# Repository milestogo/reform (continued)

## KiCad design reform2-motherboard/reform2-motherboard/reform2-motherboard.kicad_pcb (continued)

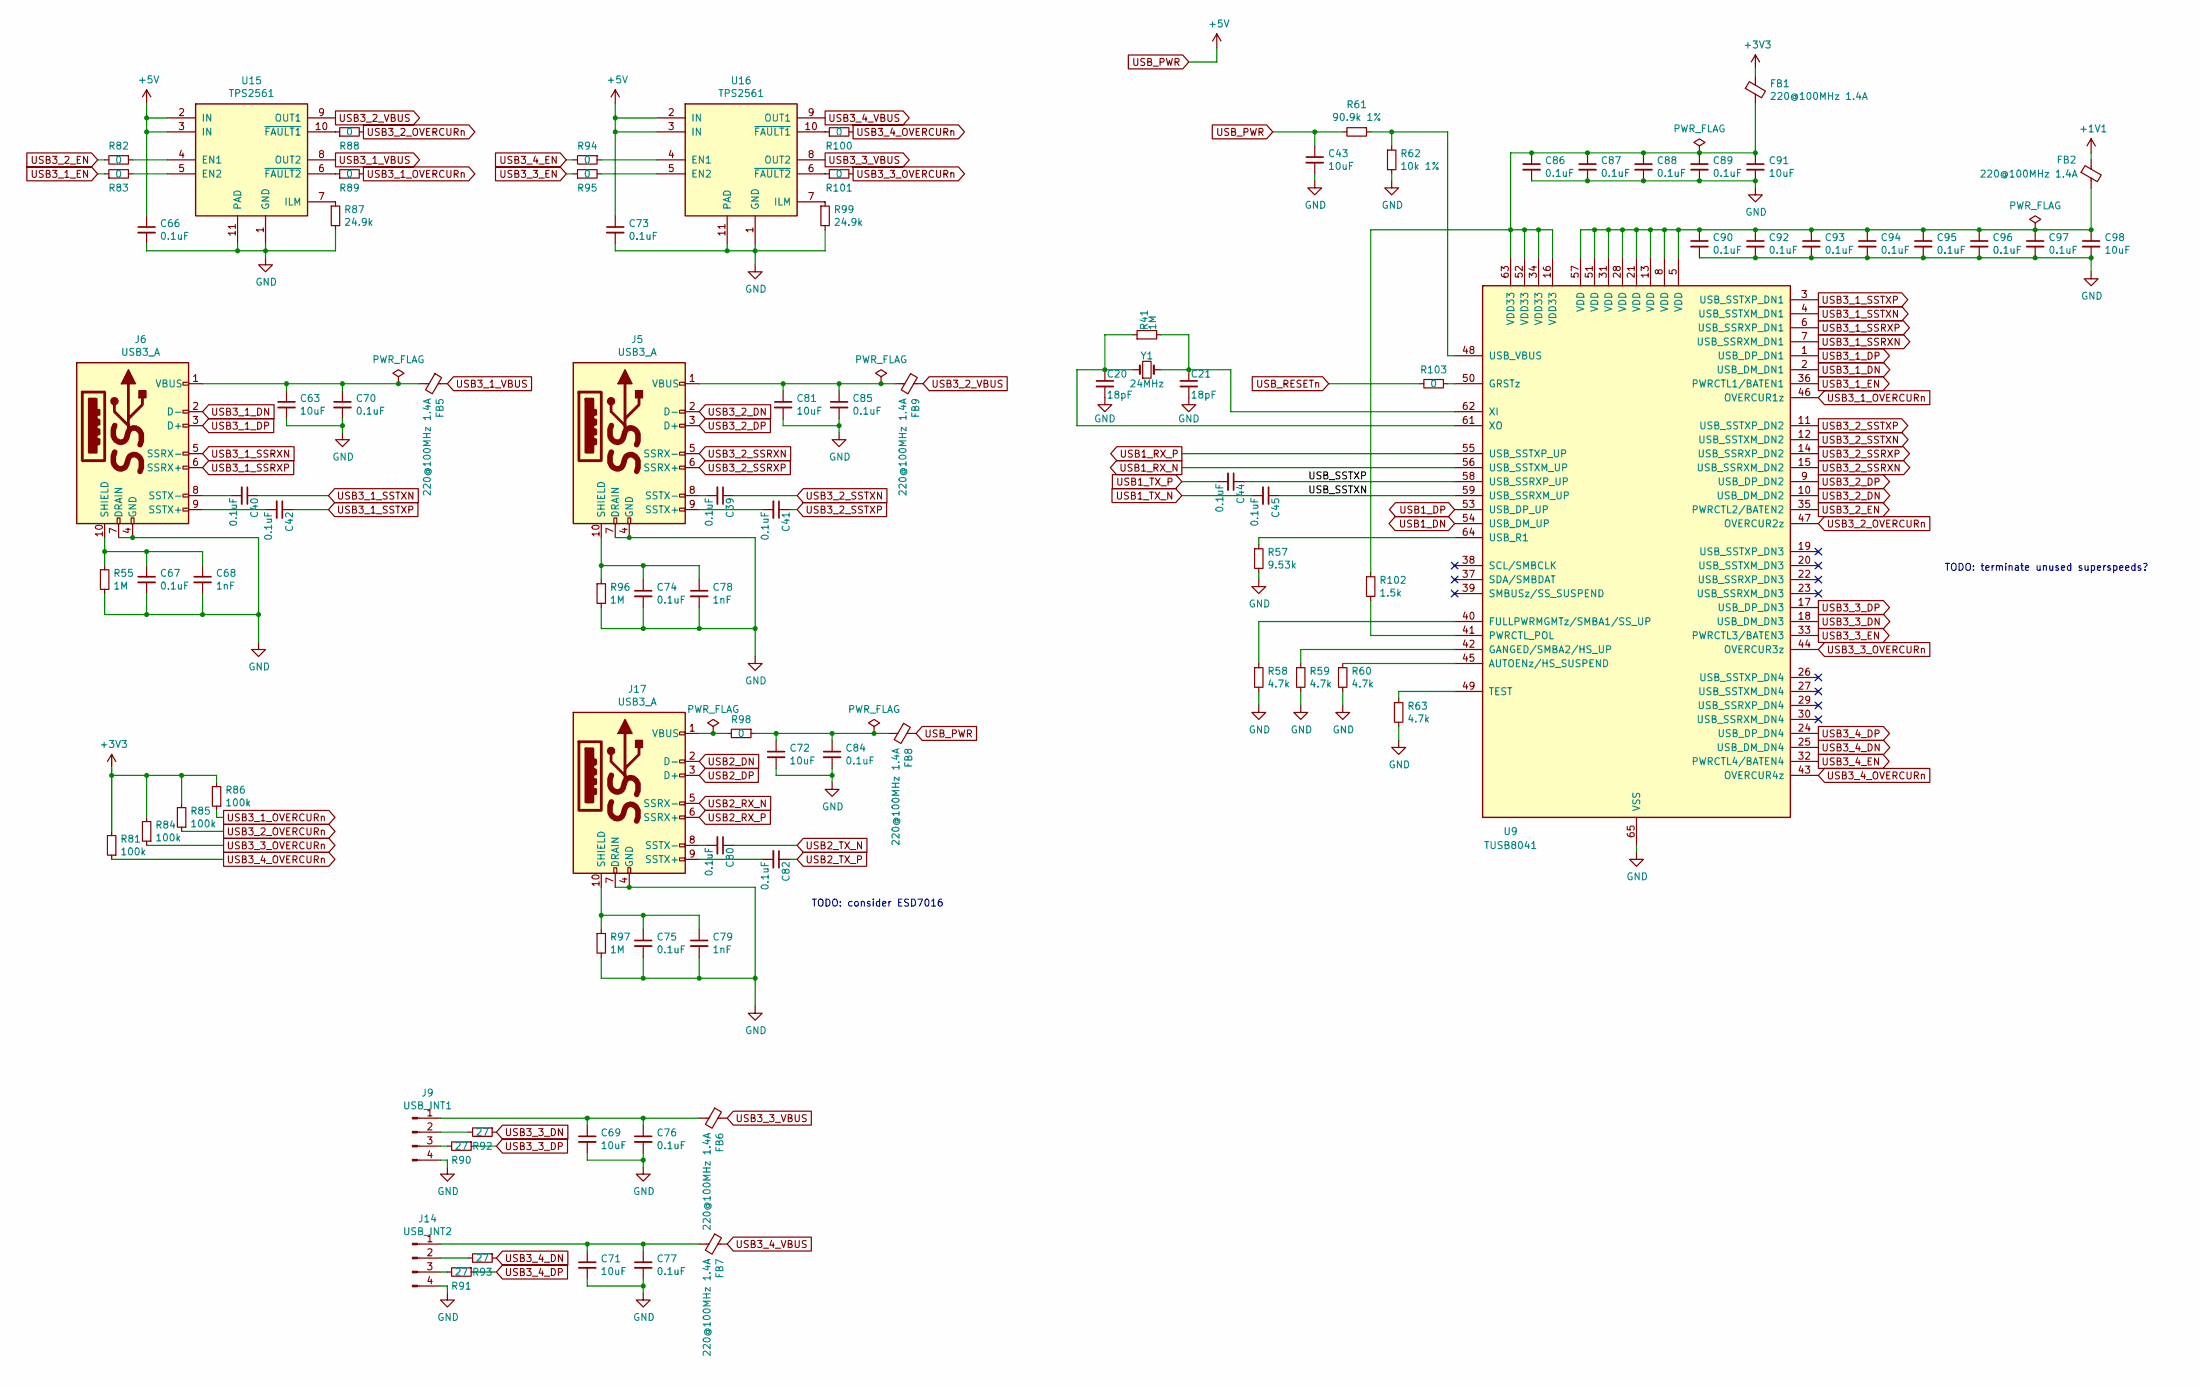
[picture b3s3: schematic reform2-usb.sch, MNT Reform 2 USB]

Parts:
C20, C21: 18pF; C_0603_1608Metric
C39, C40, C41, C42, C44, C45, C66, C67, C70, C73, C74, C75, C76, C77, C80, C82, C84, C85, C86, C87, C88, C89, C90, C92, C93, C94, C95, C96, C97: 0.1uF; C_0603_1608Metric
C43, C63, C69, C71, C72, C81, C91, C98: 10uF; C_0603_1608Metric
C68, C78, C79: 1nF; C_0603_1608Metric
FB1, FB2, FB5, FB6, FB7, FB8, FB9: 220@100MHz 1.4A; L_0603_1608Metric
J5, J6, J17: USB3_A; USB3_A_Molex_48393-001
J9: USB_INT1; PinHeader_1x04_P2.00mm_Horizontal
J14: USB_INT2; PinHeader_1x04_P2.00mm_Horizontal
R41, R55, R96, R97: 1M; R_0603_1608Metric
R57: 9.53k; R_0603_1608Metric
R58, R59, R60, R63: 4.7k; R_0603_1608Metric
R61: 90.9k 1%; R_0603_1608Metric
R62: 10k 1%; R_0603_1608Metric
R81, R84, R85, R86: 100k; R_0603_1608Metric
R82, R83, R88, R89, R94, R95, R98, R100, R101, R103: 0; R_0603_1608Metric
R87, R99: 24.9k; R_0603_1608Metric
R90, R91, R92, R93: 27; R_0603_1608Metric
R102: 1.5k; R_0603_1608Metric
U9: TUSB8041; QFN-64-1EP_9x9mm_P0.5mm_EP6x6mm_ThermalVias
U15, U16: TPS2561; VSON-10-1EP_3x3mm_P0.5mm_EP1.65x2.4mm_ThermalVias
Y1: 24MHz; Crystal_SMD_Abracon_ABM8G-4Pin_3.2x2.5mm

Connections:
+1V1: FB2.1; also elsewhere on the board
/Reform 2 USB/USB_SSTXN: C45.1, U9.59 (USB_SSRXM_UP)
/Reform 2 USB/USB_SSTXP: C44.1, U9.58 (USB_SSRXP_UP)
GND: C20.2, C21.2, C43.2, C63.2, C66.2, C67.2, C68.2, C69.2, C70.2, C71.2, C72.2, C73.2, C74.2, C75.2, C76.2, C77.2, C78.2, C79.2, C81.2, C84.2, C85.2, C86.2, C87.2, C88.2, C89.2, C90.2, C91.2, C92.2, C93.2, C94.2, C95.2, C96.2, C97.2, C98.2, J5.4 (GND), J5.7 (DRAIN), J6.4 (GND), J6.7 (DRAIN), J9.4, J14.4, J17.4 (GND), J17.7 (DRAIN), R55.2, R57.2, R58.2, R59.2, R60.2, R62.2, R63.2, R87.2, R96.2, R97.2, R99.2, U9.65 (VSS), U15.1 (GND), U15.11 (PAD), U16.1 (GND), U16.11 (PAD); also elsewhere on the board
unnamed: C20.1, R41.1, U9.61 (XO), Y1.1
unnamed: C21.1, R41.2, U9.62 (XI), Y1.2
unnamed: C39.2, J5.8 (SSTX-)
unnamed: C40.2, J6.8 (SSTX-)
unnamed: C41.2, J5.9 (SSTX+)
unnamed: C42.2, J6.9 (SSTX+)
unnamed: C63.1, C70.1, FB5.2, J6.1 (VBUS)
unnamed: C67.1, C68.1, J6.10 (SHIELD), R55.1
unnamed: C69.1, C76.1, FB6.2, J9.1
unnamed: C71.1, C77.1, FB7.2, J14.1
unnamed: C72.1, C84.1, FB8.2, R98.1
unnamed: C74.1, C78.1, J5.10 (SHIELD), R96.1
unnamed: C75.1, C79.1, J17.10 (SHIELD), R97.1
unnamed: C80.2, J17.8 (SSTX-)
unnamed: C81.1, C85.1, FB9.2, J5.1 (VBUS)
unnamed: C82.2, J17.9 (SSTX+)
unnamed: C86.1, C87.1, C88.1, C89.1, C91.1, FB1.2, R102.1, U9.16 (VDD33), U9.34 (VDD33), U9.52 (VDD33), U9.63 (VDD33)
unnamed: C90.1, C92.1, C93.1, C94.1, C95.1, C96.1, C97.1, C98.1, FB2.2, U9.5 (VDD), U9.8 (VDD), U9.13 (VDD), U9.21 (VDD), U9.28 (VDD), U9.31 (VDD), U9.51 (VDD), U9.57 (VDD)
unnamed: J9.2, R92.2
unnamed: J9.3, R90.2
unnamed: J14.2, R93.2
unnamed: J14.3, R91.2
unnamed: J17.1 (VBUS), R98.2
unnamed: R57.1, U9.64 (USB_R1)
unnamed: R58.1, U9.40 (FULLPWRMGMTz/SMBA1/SS_UP)
unnamed: R59.1, U9.42 (GANGED/SMBA2/HS_UP)
unnamed: R60.1, U9.45 (AUTOENz/HS_SUSPEND)
unnamed: R61.1, R62.1, U9.48 (USB_VBUS)
unnamed: R63.1, U9.49 (TEST)
unnamed: R82.1, U15.4 (EN1)
unnamed: R83.2, U15.5 (EN2)
unnamed: R87.1, U15.7 (ILM)
unnamed: R88.1, U15.10 (~FAULT1)
unnamed: R89.1, U15.6 (~FAULT2)
unnamed: R94.1, U16.4 (EN1)
unnamed: R95.2, U16.5 (EN2)
unnamed: R99.1, U16.7 (ILM)
unnamed: R100.1, U16.10 (~FAULT1)
unnamed: R101.1, U16.6 (~FAULT2)
unnamed: R102.2, U9.41 (PWRCTL_POL)
unnamed: R103.1, U9.50 (GRSTz)
USB1_DN: U9.54 (USB_DM_UP); also elsewhere on the board
USB1_DP: U9.53 (USB_DP_UP); also elsewhere on the board
USB1_RX_N: U9.56 (USB_SSTXM_UP); also elsewhere on the board
USB1_RX_P: U9.55 (USB_SSTXP_UP); also elsewhere on the board
USB1_TX_N: C45.2; also elsewhere on the board
USB1_TX_P: C44.2; also elsewhere on the board
USB2_DN: J17.2 (D-); also elsewhere on the board
USB2_DP: J17.3 (D+); also elsewhere on the board
USB2_RX_N: J17.5 (SSRX-); also elsewhere on the board
USB2_RX_P: J17.6 (SSRX+); also elsewhere on the board
USB2_TX_N: C80.1; also elsewhere on the board
USB2_TX_P: C82.1; also elsewhere on the board
USB3_1_DN: J6.2 (D-), U9.2 (USB_DM_DN1)
USB3_1_DP: J6.3 (D+), U9.1 (USB_DP_DN1)
USB3_1_EN: R83.1, U9.36 (PWRCTL1/BATEN1)
USB3_1_OVERCURn: R86.1, R89.2, U9.46 (OVERCUR1z)
USB3_1_SSRXN: J6.5 (SSRX-), U9.7 (USB_SSRXM_DN1)
USB3_1_SSRXP: J6.6 (SSRX+), U9.6 (USB_SSRXP_DN1)
USB3_1_SSTXN: C40.1, U9.4 (USB_SSTXM_DN1)
USB3_1_SSTXP: C42.1, U9.3 (USB_SSTXP_DN1)
USB3_1_VBUS: FB5.1, U15.8 (OUT2)
USB3_2_DN: J5.2 (D-), U9.10 (USB_DM_DN2)
USB3_2_DP: J5.3 (D+), U9.9 (USB_DP_DN2)
USB3_2_EN: R82.2, U9.35 (PWRCTL2/BATEN2)
USB3_2_OVERCURn: R85.1, R88.2, U9.47 (OVERCUR2z)
USB3_2_SSRXN: J5.5 (SSRX-), U9.15 (USB_SSRXM_DN2)
USB3_2_SSRXP: J5.6 (SSRX+), U9.14 (USB_SSRXP_DN2)
USB3_2_SSTXN: C39.1, U9.12 (USB_SSTXM_DN2)
USB3_2_SSTXP: C41.1, U9.11 (USB_SSTXP_DN2)
USB3_2_VBUS: FB9.1, U15.9 (OUT1)
USB3_3_DN: R92.1, U9.18 (USB_DM_DN3)
USB3_3_DP: R90.1, U9.17 (USB_DP_DN3)
USB3_3_EN: R95.1, U9.33 (PWRCTL3/BATEN3)
USB3_3_OVERCURn: R84.1, R101.2, U9.44 (OVERCUR3z)
USB3_3_VBUS: FB6.1, U16.8 (OUT2)
USB3_4_DN: R93.1, U9.25 (USB_DM_DN4)
USB3_4_DP: R91.1, U9.24 (USB_DP_DN4)
USB3_4_EN: R94.2, U9.32 (PWRCTL4/BATEN4)
USB3_4_OVERCURn: R81.1, R100.2, U9.43 (OVERCUR4z)
USB3_4_VBUS: FB7.1, U16.9 (OUT1)
USB_PWR: C43.1, C66.1, C73.1, FB8.1, R61.2, U15.2 (IN), U15.3 (IN), U16.2 (IN), U16.3 (IN); also elsewhere on the board
USB_RESETn: R103.2; also elsewhere on the board

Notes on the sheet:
TODO: consider ESD7016
TODO: terminate unused superspeeds?

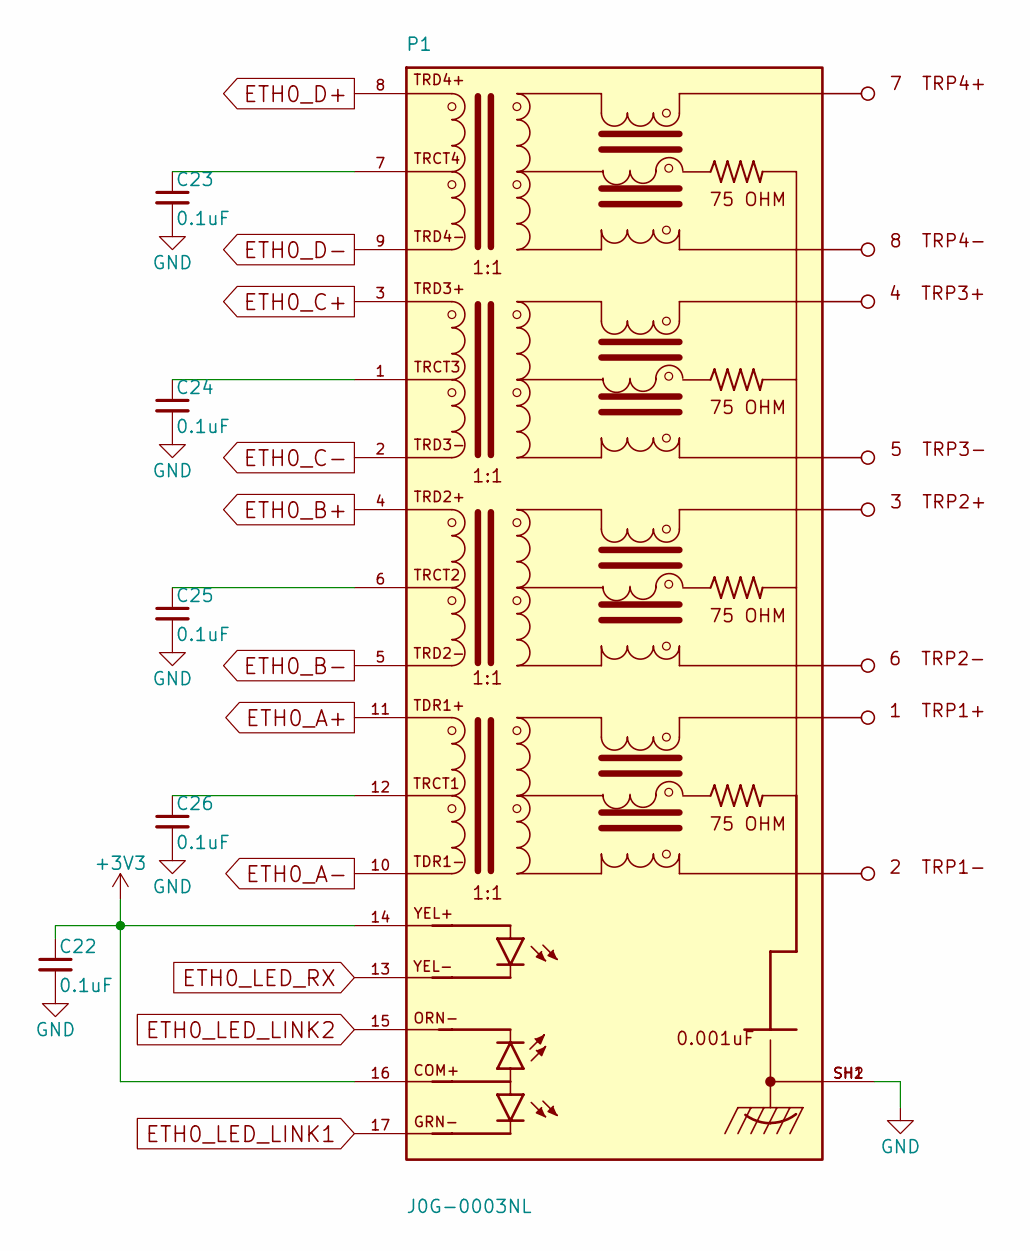
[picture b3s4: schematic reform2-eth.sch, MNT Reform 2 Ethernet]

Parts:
C22, C23, C24, C25, C26: 0.1uF; C_0603_1608Metric
P1: J0G-0003NL; PULSE_J0G-0003NL

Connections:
ETH0_A+: P1.11 (TDR1+); also elsewhere on the board
ETH0_A-: P1.10 (TDR1-); also elsewhere on the board
ETH0_B+: P1.4 (TRD2+); also elsewhere on the board
ETH0_B-: P1.5 (TRD2-); also elsewhere on the board
ETH0_C+: P1.3 (TRD3+); also elsewhere on the board
ETH0_C-: P1.2 (TRD3-); also elsewhere on the board
ETH0_D+: P1.8 (TRD4+); also elsewhere on the board
ETH0_D-: P1.9 (TRD4-); also elsewhere on the board
ETH0_LED_LINK1: P1.17 (GRN-); also elsewhere on the board
ETH0_LED_LINK2: P1.15 (ORN-); also elsewhere on the board
ETH0_LED_RX: P1.13 (YEL-); also elsewhere on the board
GND: C22.2, C23.2, C24.2, C25.2, C26.2, P1.SH1 (SHIELD), P1.SH2 (SHIELD); also elsewhere on the board
unnamed: C23.1, P1.7 (TRCT4)
unnamed: C24.1, P1.1 (TRCT3)
unnamed: C25.1, P1.6 (TRCT2)
unnamed: C26.1, P1.12 (TRCT1)

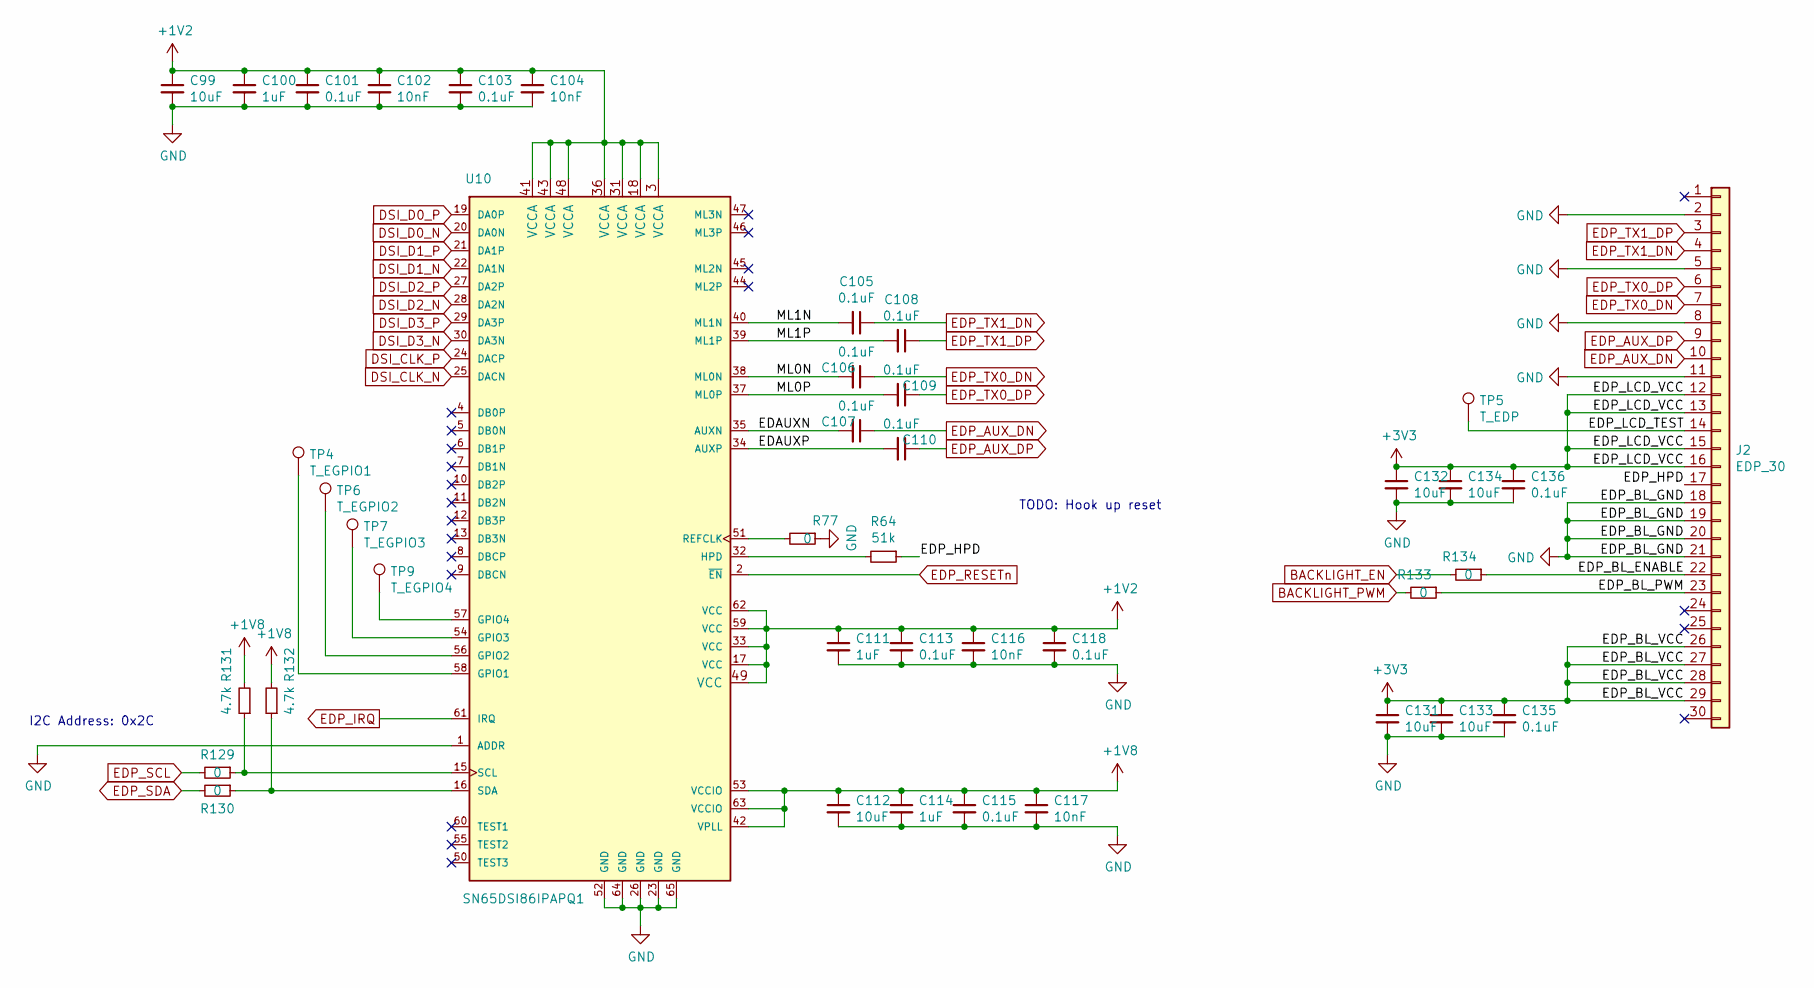
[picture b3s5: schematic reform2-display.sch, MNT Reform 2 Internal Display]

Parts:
C99, C112, C131, C132, C133, C134: 10uF; C_0603_1608Metric
C100, C111, C114: 1uF; C_0603_1608Metric
C101, C103, C105, C106, C107, C108, C109, C110, C113, C115, C118, C135, C136: 0.1uF; C_0603_1608Metric
C102, C104, C116, C117: 10nF; C_0603_1608Metric
J2: EDP_30; Hirose_FH12-30S-0.5SH_1x30-1MP_P0.50mm_Horizontal
R64: 51k; R_0603_1608Metric
R77, R129, R130, R133, R134: 0; R_0603_1608Metric
R131, R132: 4.7k; R_0603_1608Metric
TP4: T_EGPIO1; TestPoint_Pad_D1.0mm
TP5: T_EDP; TestPoint_Pad_D1.0mm
TP6: T_EGPIO2; TestPoint_Pad_D1.0mm
TP7: T_EGPIO3; TestPoint_Pad_D1.0mm
TP9: T_EGPIO4; TestPoint_Pad_D1.0mm
U10: SN65DSI86IPAPQ1; HTQFP-64-1EP_10x10mm_P0.5mm_EP8x8mm

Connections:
+1V2: C99.1, C100.1, C101.1, C102.1, C103.1, C104.1, C111.1, C113.1, C116.1, C118.1, U10.3 (VCCA), U10.17 (VCC), U10.18 (VCCA), U10.31 (VCCA), U10.33 (VCC), U10.36 (VCCA), U10.41 (VCCA), U10.43 (VCCA), U10.48 (VCCA), U10.49 (VCC), U10.59 (VCC), U10.62 (VCC); also elsewhere on the board
+1V8: C112.1, C114.1, C115.1, C117.1, R131.2, R132.2, U10.42 (VPLL), U10.53 (VCCIO), U10.63 (VCCIO); also elsewhere on the board
/Reform 2 Display/EDAUXN: C107.2, U10.35 (AUXN)
/Reform 2 Display/EDAUXP: C110.2, U10.34 (AUXP)
/Reform 2 Display/EDP_BL_ENABLE: J2.22, R134.1
/Reform 2 Display/EDP_BL_PWM: J2.23, R133.1
/Reform 2 Display/EDP_HPD: J2.17, R64.1
/Reform 2 Display/EDP_LCD_TEST: J2.14, TP5.1
/Reform 2 Display/ML0N: C106.2, U10.38 (ML0N)
/Reform 2 Display/ML0P: C109.2, U10.37 (ML0P)
/Reform 2 Display/ML1N: C105.2, U10.40 (ML1N)
/Reform 2 Display/ML1P: C108.2, U10.39 (ML1P)
BACKLIGHT_EN: R134.2; also elsewhere on the board
BACKLIGHT_PWM: R133.2; also elsewhere on the board
DSI_CLK_N: U10.25 (DACN); also elsewhere on the board
DSI_CLK_P: U10.24 (DACP); also elsewhere on the board
DSI_D0_N: U10.20 (DA0N); also elsewhere on the board
DSI_D0_P: U10.19 (DA0P); also elsewhere on the board
DSI_D1_N: U10.22 (DA1N); also elsewhere on the board
DSI_D1_P: U10.21 (DA1P); also elsewhere on the board
DSI_D2_N: U10.28 (DA2N); also elsewhere on the board
DSI_D2_P: U10.27 (DA2P); also elsewhere on the board
DSI_D3_N: U10.30 (DA3N); also elsewhere on the board
DSI_D3_P: U10.29 (DA3P); also elsewhere on the board
EDP_AUX_DN: C107.1, J2.10
EDP_AUX_DP: C110.1, J2.9
EDP_IRQ: U10.61 (IRQ); also elsewhere on the board
EDP_RESETn: U10.2 (~EN~); also elsewhere on the board
EDP_SCL: R129.2; also elsewhere on the board
EDP_SDA: R130.2; also elsewhere on the board
EDP_TX0_DN: C106.1, J2.7
EDP_TX0_DP: C109.1, J2.6
EDP_TX1_DN: C105.1, J2.4
EDP_TX1_DP: C108.1, J2.3
GND: C99.2, C100.2, C101.2, C102.2, C103.2, C104.2, C111.2, C112.2, C113.2, C114.2, C115.2, C116.2, C117.2, C118.2, C131.2, C132.2, C133.2, C134.2, C135.2, C136.2, J2.2, J2.5, J2.8, J2.11, J2.18, J2.19, J2.20, J2.21, R77.1, U10.1 (ADDR), U10.23 (GND), U10.26 (GND), U10.52 (GND), U10.64 (GND), U10.65 (GND); also elsewhere on the board
unnamed: R64.2, U10.32 (HPD)
unnamed: R77.2, U10.51 (REFCLK)
unnamed: R129.1, R131.1, U10.15 (SCL)
unnamed: R130.1, R132.1, U10.16 (SDA)
unnamed: TP4.1, U10.58 (GPIO1)
unnamed: TP6.1, U10.56 (GPIO2)
unnamed: TP7.1, U10.54 (GPIO3)
unnamed: TP9.1, U10.57 (GPIO4)

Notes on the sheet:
TODO: Hook up reset
I2C Address: 0x2C

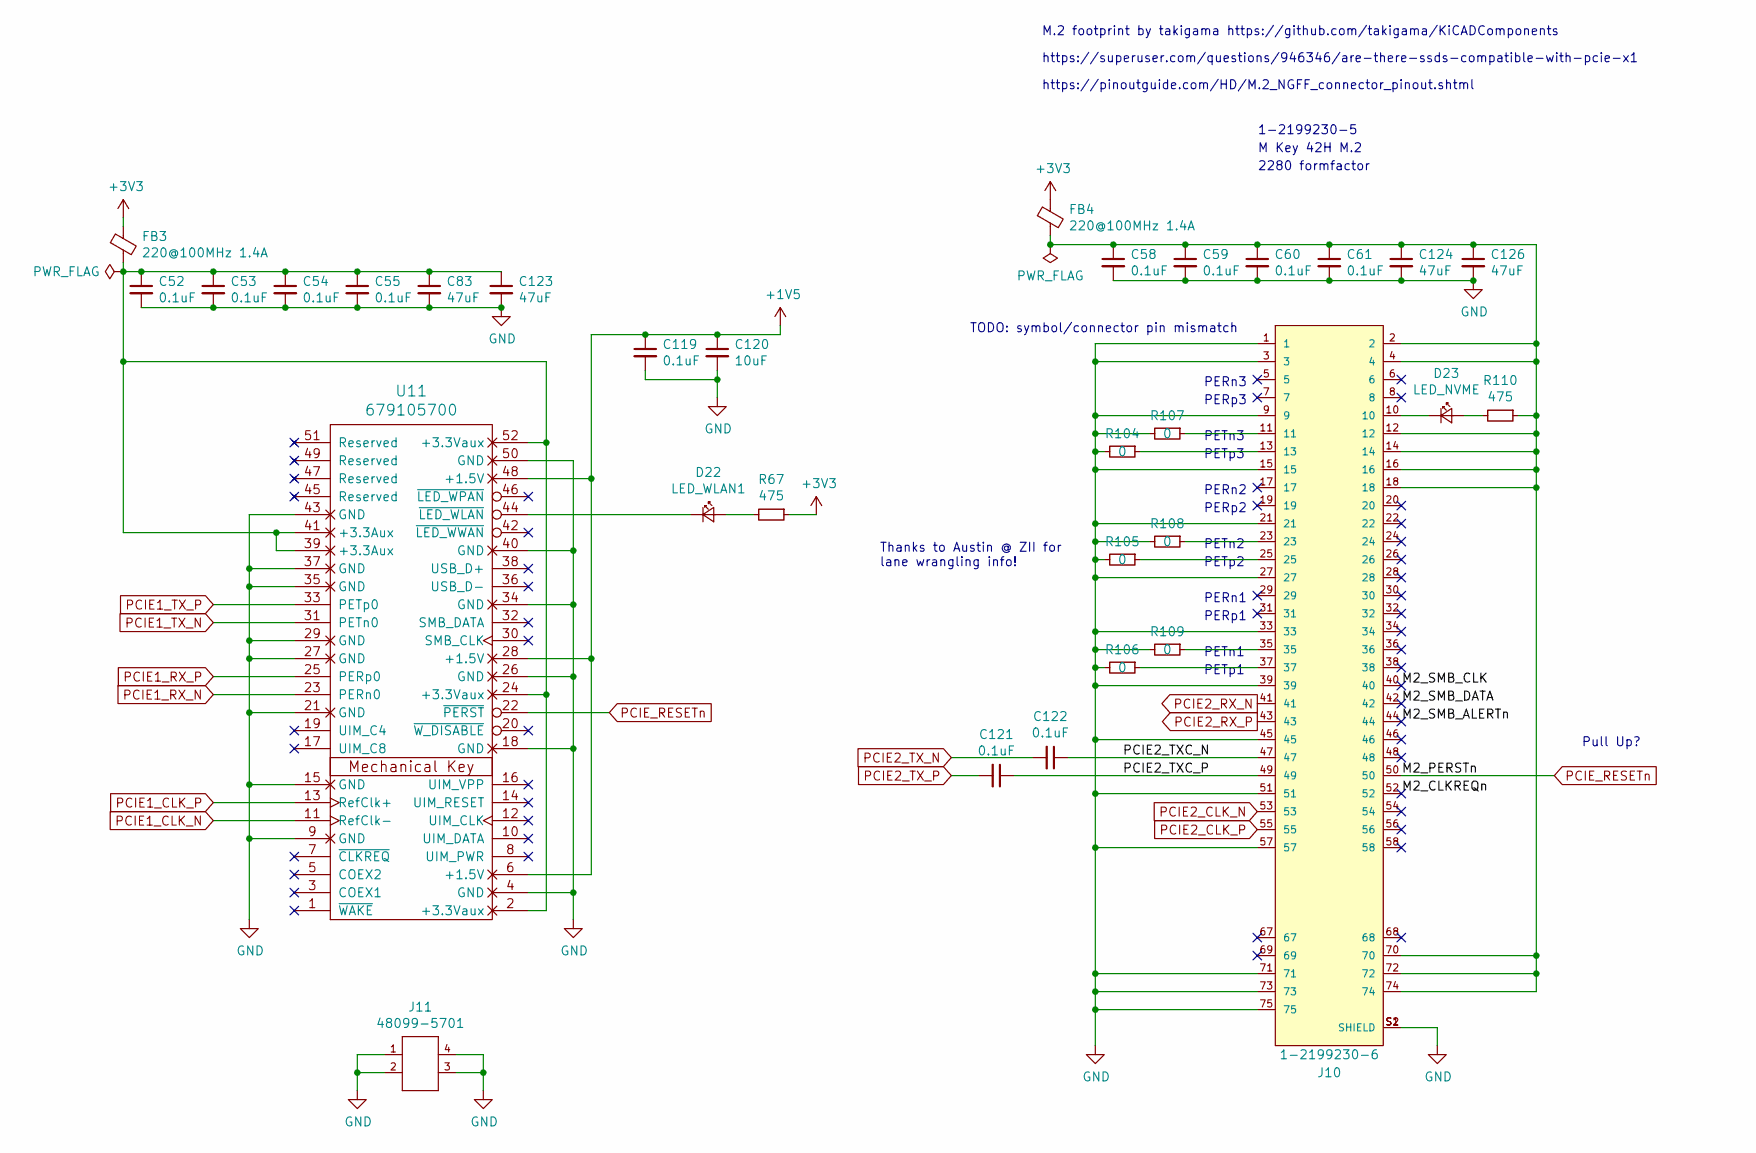
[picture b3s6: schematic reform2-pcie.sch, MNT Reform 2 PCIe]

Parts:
C52, C53, C54, C55, C58, C59, C60, C61, C119, C121, C122: 0.1uF; C_0603_1608Metric
C83, C123, C124, C126: 47uF; C_0603_1608Metric
C120: 10uF; C_0603_1608Metric
D22: LED_WLAN1; LED_0603_1608Metric
D23: LED_NVME; LED_0603_1608Metric
FB3, FB4: 220@100MHz 1.4A; L_0603_1608Metric
J10: 1-2199230-6; TE_1-2199230-6
J11: 48099-5701; MOLEX_48099-5701
R67, R110: 475; R_0603_1608Metric
R104, R105, R106, R107, R108, R109: 0; R_0603_1608Metric
U11: 679105700; MOLEX_67910-5700

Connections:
+1V5: C119.1, C120.1, U11.6 (+1.5V), U11.28 (+1.5V), U11.48 (+1.5V); also elsewhere on the board
/Reform 2 PCIe/M2_CLKREQn: J10.52
/Reform 2 PCIe/M2_SMB_ALERTn: J10.44
/Reform 2 PCIe/M2_SMB_CLK: J10.40
/Reform 2 PCIe/M2_SMB_DATA: J10.42
/Reform 2 PCIe/PCIE2_TXC_N: C122.1, J10.47
/Reform 2 PCIe/PCIE2_TXC_P: C121.1, J10.49
GND: C52.2, C53.2, C54.2, C55.2, C58.2, C59.2, C60.2, C61.2, C83.2, C119.2, C120.2, C123.2, C124.2, C126.2, J10.1, J10.3, J10.9, J10.15, J10.21, J10.27, J10.33, J10.39, J10.45, J10.51, J10.57, J10.71, J10.73, J10.75, J10.S1 (SHIELD), J10.S2 (SHIELD), J11.1, J11.2, J11.3, J11.4, R104.2, R105.2, R106.2, R107.2, R108.2, R109.2, U11.4 (GND), U11.9 (GND), U11.15 (GND), U11.18 (GND), U11.21 (GND), U11.26 (GND), U11.27 (GND), U11.29 (GND), U11.34 (GND), U11.35 (GND), U11.37 (GND), U11.40 (GND), U11.43 (GND), U11.50 (GND); also elsewhere on the board
unnamed: C52.1, C53.1, C54.1, C55.1, C83.1, C123.1, FB3.2, U11.2 (+3.3Vaux), U11.24 (+3.3Vaux), U11.39 (+3.3Aux), U11.41 (+3.3Aux), U11.52 (+3.3Vaux)
unnamed: C58.1, C59.1, C60.1, C61.1, C124.1, C126.1, FB4.2, J10.2, J10.4, J10.12, J10.14, J10.16, J10.18, J10.70, J10.72, J10.74, R110.1
unnamed: D22.1 (K), U11.44 (~LED_WLAN)
unnamed: D22.2 (A), R67.2
unnamed: D23.1 (K), J10.10
unnamed: D23.2 (A), R110.2
unnamed: J10.11, R107.1
unnamed: J10.13, R104.1
unnamed: J10.23, R108.1
unnamed: J10.25, R105.1
unnamed: J10.35, R109.1
unnamed: J10.37, R106.1
PCIE1_CLK_N: U11.11 (RefClk-); also elsewhere on the board
PCIE1_CLK_P: U11.13 (RefClk+); also elsewhere on the board
PCIE1_RX_N: U11.23 (PERn0); also elsewhere on the board
PCIE1_RX_P: U11.25 (PERp0); also elsewhere on the board
PCIE1_TX_N: U11.31 (PETn0); also elsewhere on the board
PCIE1_TX_P: U11.33 (PETp0); also elsewhere on the board
PCIE2_CLK_N: J10.53; also elsewhere on the board
PCIE2_CLK_P: J10.55; also elsewhere on the board
PCIE2_RX_N: J10.41; also elsewhere on the board
PCIE2_RX_P: J10.43; also elsewhere on the board
PCIE2_TX_N: C122.2; also elsewhere on the board
PCIE2_TX_P: C121.2; also elsewhere on the board
PCIE_RESETn: J10.50, U11.22 (~PERST); also elsewhere on the board

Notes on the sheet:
1-2199230-5
M Key 42H M.2
2280 formfactor
M.2 footprint by takigama https://github.com/takigama/KiCADComponents
https://superuser.com/questions/946346/are-there-ssds-compatible-with-pcie-x1
https://pinoutguide.com/HD/M.2_NGFF_connector_pinout.shtml
Pull Up?
PERn1
PERp1
PETp2
PETn2
PETn1
PETp1
PERn2
PERp2
PETp3
PETn3
PERn3
PERp3
Thanks to Austin @ ZII for lane wrangling info!
TODO: symbol/connector pin mismatch

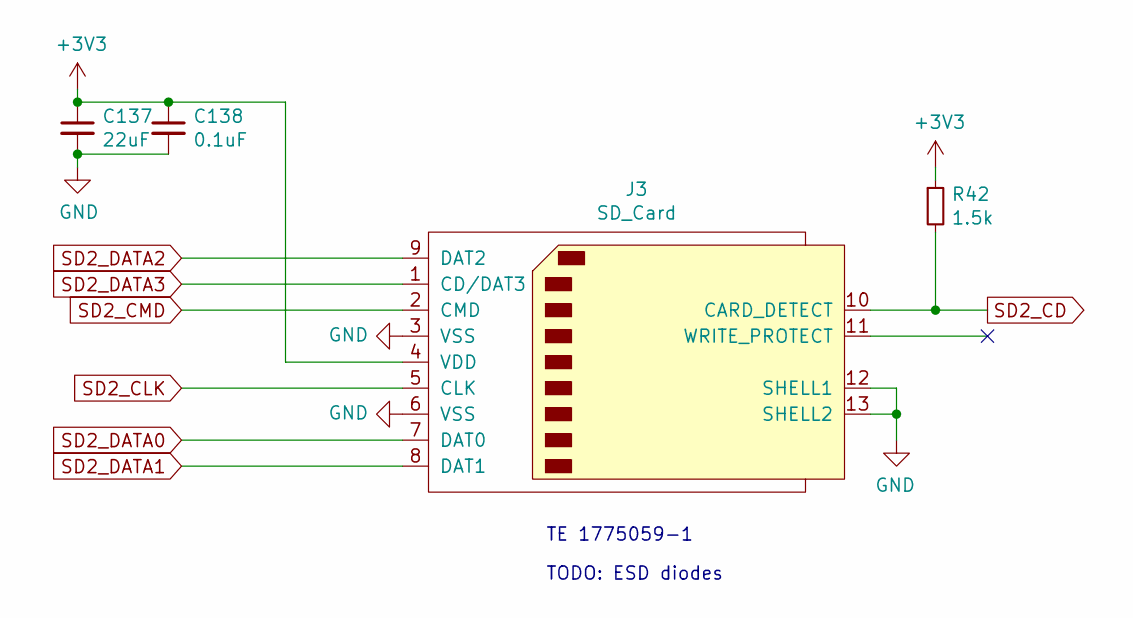
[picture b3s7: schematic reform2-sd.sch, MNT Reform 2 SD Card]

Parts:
C137: 22uF; C_0603_1608Metric
C138: 0.1uF; C_0603_1608Metric
J3: SD_Card; TE_1775059-1
R42: 1.5k; R_0603_1608Metric

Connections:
GND: C137.2, C138.2, J3.3 (VSS), J3.6 (VSS), J3.12 (SHELL1), J3.13 (SHELL2); also elsewhere on the board
SD2_CD: J3.10 (CARD_DETECT), R42.2; also elsewhere on the board
SD2_CLK: J3.5 (CLK); also elsewhere on the board
SD2_CMD: J3.2 (CMD); also elsewhere on the board
SD2_DATA0: J3.7 (DAT0); also elsewhere on the board
SD2_DATA1: J3.8 (DAT1); also elsewhere on the board
SD2_DATA2: J3.9 (DAT2); also elsewhere on the board
SD2_DATA3: J3.1 (CD/DAT3); also elsewhere on the board

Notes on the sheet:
TODO: ESD diodes
TE 1775059-1

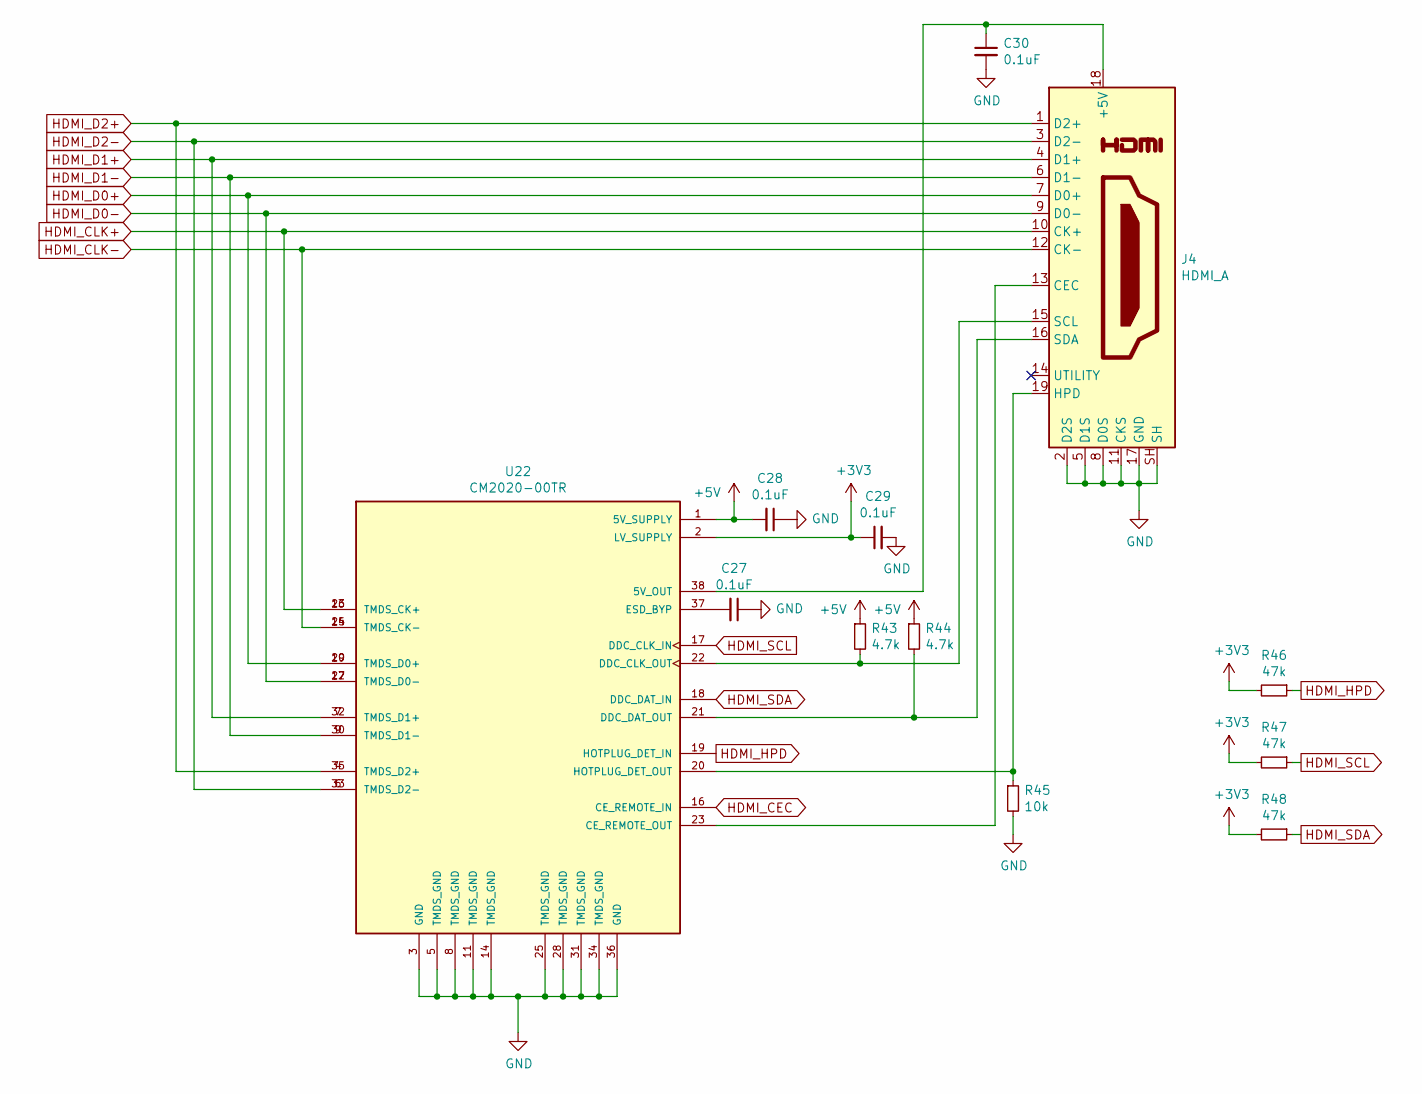
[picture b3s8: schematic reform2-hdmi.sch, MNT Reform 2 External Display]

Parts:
C27, C28, C29, C30: 0.1uF; C_0603_1608Metric
J4: HDMI_A; HDMI-685119134923
R43, R44: 4.7k; R_0603_1608Metric
R45: 10k; R_0603_1608Metric
R46, R47, R48: 47k; R_0603_1608Metric
U22: CM2020-00TR; TSSOP50P640X120-38N

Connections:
GND: C27.1, C28.1, C29.2, C30.2, J4.2 (D2S), J4.5 (D1S), J4.8 (D0S), J4.11 (CKS), J4.17 (GND), J4.SH, R45.2, U22.3 (GND), U22.5 (TMDS_GND), U22.8 (TMDS_GND), U22.11 (TMDS_GND), U22.14 (TMDS_GND), U22.25 (TMDS_GND), U22.28 (TMDS_GND), U22.31 (TMDS_GND), U22.34 (TMDS_GND), U22.36 (GND); also elsewhere on the board
HDMI_CEC: U22.16 (CE_REMOTE_IN); also elsewhere on the board
HDMI_CLK+: J4.10 (CK+), U22.13 (TMDS_CK+), U22.26 (TMDS_CK+); also elsewhere on the board
HDMI_CLK-: J4.12 (CK-), U22.15 (TMDS_CK-), U22.24 (TMDS_CK-); also elsewhere on the board
HDMI_D0+: J4.7 (D0+), U22.10 (TMDS_D0+), U22.29 (TMDS_D0+); also elsewhere on the board
HDMI_D0-: J4.9 (D0-), U22.12 (TMDS_D0-), U22.27 (TMDS_D0-); also elsewhere on the board
HDMI_D1+: J4.4 (D1+), U22.7 (TMDS_D1+), U22.32 (TMDS_D1+); also elsewhere on the board
HDMI_D1-: J4.6 (D1-), U22.9 (TMDS_D1-), U22.30 (TMDS_D1-); also elsewhere on the board
HDMI_D2+: J4.1 (D2+), U22.4 (TMDS_D2+), U22.35 (TMDS_D2+); also elsewhere on the board
HDMI_D2-: J4.3 (D2-), U22.6 (TMDS_D2-), U22.33 (TMDS_D2-); also elsewhere on the board
HDMI_HPD: R46.1, U22.19 (HOTPLUG_DET_IN); also elsewhere on the board
HDMI_SCL: R47.1, U22.17 (DDC_CLK_IN); also elsewhere on the board
HDMI_SDA: R48.1, U22.18 (DDC_DAT_IN); also elsewhere on the board
unnamed: C27.2, U22.37 (ESD_BYP)
unnamed: C30.1, J4.18 (+5V), U22.38 (5V_OUT)
unnamed: J4.13 (CEC), U22.23 (CE_REMOTE_OUT)
unnamed: J4.15 (SCL), R43.2, U22.22 (DDC_CLK_OUT)
unnamed: J4.16 (SDA), R44.2, U22.21 (DDC_DAT_OUT)
unnamed: J4.19 (HPD), R45.1, U22.20 (HOTPLUG_DET_OUT)
USB_PWR: C28.2, R43.1, R44.1, U22.1 (5V_SUPPLY); also elsewhere on the board

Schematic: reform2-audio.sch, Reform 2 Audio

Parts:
C127, C147: 47uF; C_0603_1608Metric
C139, C140, C141, C150, C151: 10uF; C_0603_1608Metric
C142, C143, C144, C146, C154, C157: 0.1uF; C_0603_1608Metric
C145, C155, C156: 1uF; C_0603_1608Metric
C149, C153: 10nF; C_0603_1608Metric
C152: 220pF; C_0603_1608Metric
C158, C159: 22uF; C_0603_1608Metric
J7: SJ-43516-SMT
J16: LINE_IN; PinHeader_1x03_P2.54mm_Vertical
J21: Conn_01x04_Male; PinHeader_1x04_P2.54mm_Vertical
R66, R112: 220; R_0603_1608Metric
R114, R121, R138, R139, R150, R151: 33; R_0603_1608Metric
R135, R136: 4.7k; R_0603_1608Metric
R137: 10k; R_0603_1608Metric
R140: 680; R_0603_1608Metric
R141: 2k; R_0603_1608Metric
R142, R143, R144: 47k; R_0603_1608Metric
R145, R152: 0; R_0603_1608Metric
TP1: T_GAIN; TestPoint_Pad_D1.0mm
U20: WM8731; SSOP-28_5.3x10.2mm_P0.65mm
U21: MAX9715ETE+; TQFN-16-1EP_5x5mm_P0.8mm_EP3.1x3.1mm

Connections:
DAC_BCLK: R114.1; also elsewhere on the board
DAC_DIN: R150.1; also elsewhere on the board
DAC_DOUT: R121.1; also elsewhere on the board
DAC_MCLK: R138.2; also elsewhere on the board
DAC_RXFS: R139.1; also elsewhere on the board
DAC_SCL: R66.1; also elsewhere on the board
DAC_SDA: R112.1; also elsewhere on the board
DAC_TXFS: R151.1; also elsewhere on the board
GND: C139.2, C140.2, C141.1, C142.2, C143.2, C144.1, C146.2, C150.2, C151.2, C152.2, C154.2, C155.2, C156.2, C157.2, J16.1, R137.1, R142.2, R143.2, R144.2, R145.2, U20.11 (HPGND), U20.15 (AGND), U20.28 (DGND), U21.1 (PGND), U21.7 (GND), U21.12 (PGND), U21.17 (PAD); also elsewhere on the board
unnamed: C127.1, J7.2 (TIP), R142.1
unnamed: C127.2, U20.9 (LHPOUT)
unnamed: C145.1, C152.1, J7.1 (SLEEVE), R140.2, R144.1
unnamed: C145.2, R141.2
unnamed: C147.1, J7.3 (RING1), R143.1
unnamed: C147.2, U20.10 (RHPOUT)
unnamed: C149.1, U21.15 (INR)
unnamed: C149.2, U20.13 (ROUT)
unnamed: C150.1, C154.1, U20.16 (VMID)
unnamed: C153.1, U21.16 (INL)
unnamed: C153.2, U20.12 (LOUT)
unnamed: C156.1, U21.13 (BIAS)
unnamed: C158.1, J21.4
unnamed: C158.2, U21.2 (OUTL+)
unnamed: C159.1, J21.2
unnamed: C159.2, U21.11 (OUTR+)
unnamed: J7.4 (RING2), R145.1
unnamed: J16.2, U20.19 (RLINEIN)
unnamed: J16.3, U20.20 (LLINEIN)
unnamed: J21.1, U21.10 (OUTR-)
unnamed: J21.3, U21.3 (OUTL-)
unnamed: R112.2, R136.2, U20.23 (SDIN)
unnamed: R114.2, U20.3 (BCLK)
unnamed: R121.2, U20.4 (DACDAT)
unnamed: R66.2, R135.2, U20.24 (SCLK)
unnamed: R137.2, U20.21 (MODE), U20.22 (CSB)
unnamed: R138.1, U20.25 (XTI/MCLK)
unnamed: R139.2, U20.7 (ADCLRC)
unnamed: R140.1, U20.17 (MICBIAS)
unnamed: R141.1, U20.18 (MICIN)
unnamed: R150.2, U20.6 (ADCDAT)
unnamed: R151.2, U20.5 (DACLRC)
unnamed: R152.1, U21.8 (~SHDN)
unnamed: TP1.1, U21.6 (GAIN)
USB_PWR: C155.1, C157.1, R152.2, U21.4 (PVDD), U21.9 (PVDD), U21.14 (VDD); also elsewhere on the board

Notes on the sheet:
TODO: potentially a THT connector
selects 2-wire
TODO: chokes?
CTIA standard TRRS

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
